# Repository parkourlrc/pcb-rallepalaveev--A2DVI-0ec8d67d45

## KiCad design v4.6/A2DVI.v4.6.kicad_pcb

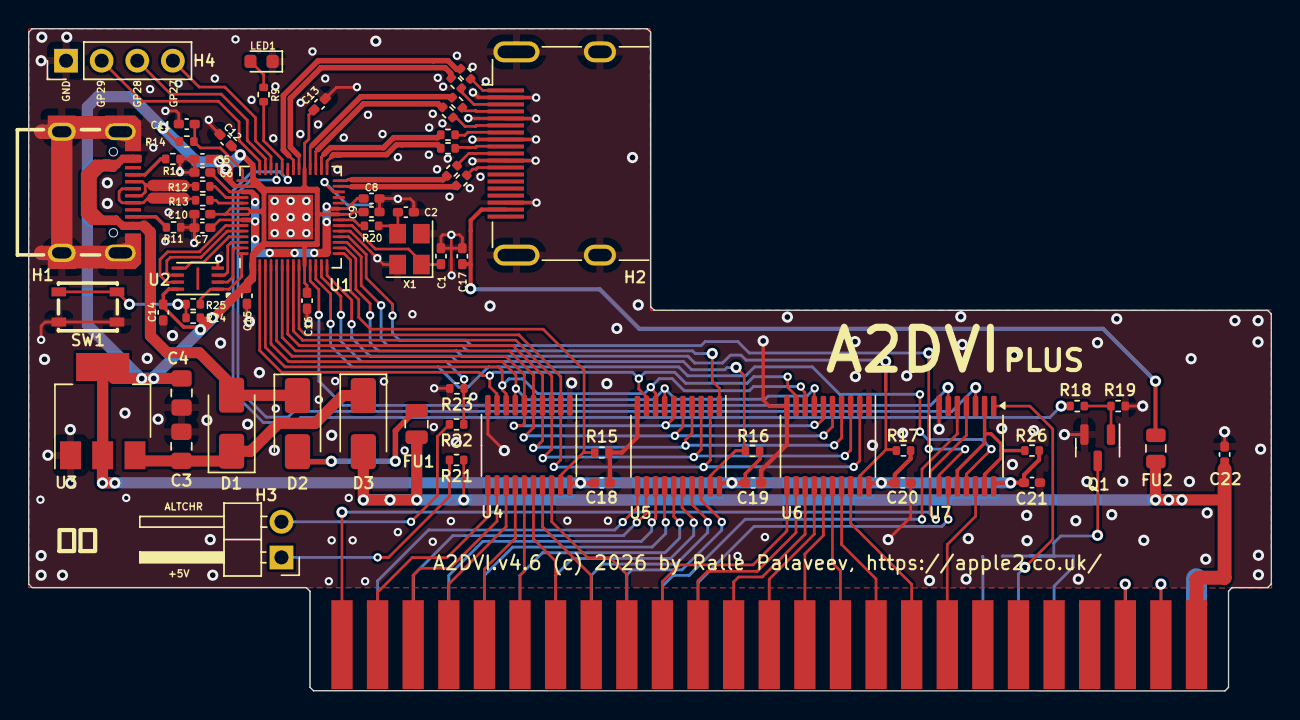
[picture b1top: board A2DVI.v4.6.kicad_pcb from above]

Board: 2 copper layers, 88.6 x 47.2 mm, 68 parts (0 on the bottom side), 60 nets.

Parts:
C1, C2: 15p; C_0402_1005Metric_Pad0.74x0.62mm_HandSolder
C3, C4: 22uF; C_0805_2012Metric_Pad1.18x1.45mm_HandSolder
C5, C6: 2u2; C_0402_1005Metric_Pad0.74x0.62mm_HandSolder
C7, C8, C9, C10, C11, C12, C13, C14, C15, C16, C17, C18, C19, C20, C21, C22: 100n; C_0402_1005Metric_Pad0.74x0.62mm_HandSolder
D1, D2, D3: SS14; D_SMA
FU1, FU2: 500mA; Fuse_0805_2012Metric
H1: USB-C-16P-F(A40-00119-A52-12); USB2.0_TYPE-C(A40-00119-A52-12)
H2: HDMI_A_Molex_208658-1001_Horizontal
H3: PinHeader_1x02_P2.54mm_Horizontal
H4: PinHeader_1x04_P2.54mm_Vertical
LED1: LED_0603_1608Metric
Q1: 2N7002; SOT-23
R1, R2, R3, R4, R5, R6, R7, R8, R14: 270; R_0402_1005Metric
R9, R18, R20, R21, R25, R26: 1k; R_0402_1005Metric
R10, R11: 5k1; R_0402_1005Metric
R12, R13: 27; R_0402_1005Metric
R15, R16, R17, R19, R23: 10k; R_0402_1005Metric
R22: 5.1k; R_0402_1005Metric
R24: 100k; R_0402_1005Metric
SW1: YTS-A016-X
U1: QFN-56-1EP_7x7mm_P0.4mm_EP3.2x3.2mm
U2: W25Q16JVUXIQ; Winbond_USON-8-1EP_3x2mm_P0.5mm_EP0.2x1.6mm
U3: AZ1117I-H-3.3; SOT-223-3_TabPin2
U4, U5, U6: SN74LVC245APWR; TSSOP-20_4.4x6.5mm_P0.65mm
U7: TSSOP-14_4.4x5mm_P0.65mm
X1: ABM8-272-T3 12MHz; Crystal_SMD_3225-4Pin_3.2x2.5mm

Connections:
1.1V: C6.2, C7.2, C8.1, U1.23, U1.45, U1.50
3.3V: C4.1, C5.2, C9.1, C10.2, C12.2, C13.1, C14.2, C15.2, C16.2, C18.1, C19.1, C20.1, C21.1, R14.1, R16.2, R17.2, R24.1, R26.2, U1.1, U1.10, U1.22, U1.33, U1.42, U1.44, U1.48, U1.49, U2.8, U3.2, U4.20, U5.20, U6.20, U7.14
3.3V_s: R26.1, U7.2, U7.10, U7.13
5V: C22.1, D3.2, FU1.2, FU2.2, R21.2
5V-1: D2.2, FU1.1
5V-2: H3.1, R21.1
5V_out: C17.2, FU2.1, H2.18
AD0: U1.2, U4.9, U5.9, U6.9
AD1: U1.3, U4.8, U5.8, U6.8
AD2: U1.4, U4.7, U5.7, U6.7
AD3: U1.5, U4.6, U5.6, U6.6
AD4: U1.6, U4.5, U5.5, U6.5
AD5: U1.7, U4.4, U5.4, U6.4
AD6: U1.8, U4.3, U5.3, U6.3
AD7: U1.9, U4.2, U5.2, U6.2
ADCVDD: C11.2, R14.2, U1.43
Altchr: H3.2, R22.1
C-A5: H1.A5, R10.1
C-B5: H1.B5, R11.1
CK_N: R8.1, R8.2, U1.27
CK_P: H2.10, R7.1, R7.2, U1.28
D0_N: H2.9, R6.1, R6.2, U1.29
D0_P: H2.7, R5.1, R5.2, U1.30
D1_N: H2.6, R4.1, R4.2, U1.31
D1_P: H2.4, R3.1, R3.2, U1.32
D2_N: H2.3, R2.1, R2.2, U1.34
D2_P: H2.1, R1.1, R1.2, U1.35
DATADIR: U1.17, U5.1
DATAOE: R16.1, U1.14, U5.19
GND: C1.1, C2.2, C3.1, C4.2, C5.1, C6.1, C7.1, C8.2, C9.2, C10.1, C11.1, C12.1, C13.2, C14.1, C15.1, C16.1, C17.1, C18.2, C19.2, C20.2, C21.2, C22.2, H1.0, H1.A1, H1.A12, H1.B1, H1.B12, H2.2, H2.5, H2.8, H2.11, H2.17, H2.SH, H4.1, LED1.1, Q1.2, R10.2, R11.2, R15.2, R19.2, R23.1, SW1.2, U1.19, U1.57, U2.4, U3.1, U4.1, U4.10, U5.10, U6.1, U6.10, U7.7, X1.2, X1.4
GP25: R9.2, U1.37
GP27: H4.4, U1.39
GP28: H4.3, U1.40
GP29: H4.2, U1.41
IRQ-i: Q1.1, R18.2, R19.1
L-Altchr: R22.2, R23.2, U1.13
L-IRQ: R18.1, U1.36
L-PHI0: U1.18, U7.8
L-RW: U1.12, U7.11
L-Reset: U1.38, U7.3
LED: LED1.2, R9.1
LSBOE: R15.1, U1.15, U4.19
MSBOE: R17.1, U1.16, U6.19
QSPI_SCLK: U1.52, U2.6
QSPI_SD0: U1.53, U2.5
QSPI_SD1: U1.55, U2.2
QSPI_SD2: U1.54, U2.3
QSPI_SD3: U1.51, U2.7
QSPI_SS: R25.2, U1.56, U2.1
SW: R24.2, R25.1, SW1.1
Select: U1.11, U7.6
USB_DM: H1.A7, H1.B7, R12.1
USB_DMX: R12.2, U1.46
USB_DP: H1.A6, H1.B6, R13.1
USB_DPX: R13.2, U1.47
VBUS: D1.2, D2.1, H1.A4, H1.A9, H1.B4, H1.B9
VSYS: C3.2, D1.1, D3.1, U3.3
XIN: C1.2, U1.20, X1.1
XOUT: R20.1, U1.21
XOUT1: C2.1, R20.2, X1.3

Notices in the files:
v4.6/A2DVI.v4.6.kicad_pcb:
Board design by Ralle Palaveev, (c) 2026
Firmware by Thorsten Brehm, (c) 2026
A2DVI.v4.6 (c) 2026 by Ralle Palaveev, https://apple2.co.uk
